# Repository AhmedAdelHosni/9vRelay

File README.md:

# 9vRelay
Relay board operated by 9v. Still in desgning phase.

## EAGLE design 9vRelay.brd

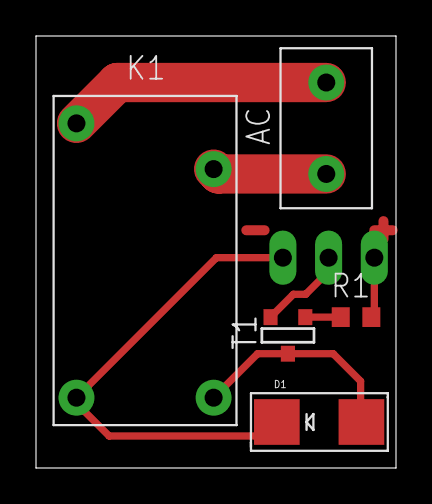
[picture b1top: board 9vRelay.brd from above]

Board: 2 copper layers, 20.0 x 24.0 mm, 6 parts (1 on the bottom side), 7 nets.

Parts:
AC: TBLOCK1X2
D1: SMADIODE
K1: OJE-SS-109LMH
R1: R0603
T1: 2N3904; SOT-23
X1: 22-23-2031

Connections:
unnamed: D1.A, K1.2, T1.1
unnamed: D1.C, K1.1, X1.3
unnamed: R1.1, X1.1
unnamed: AC.2, K1.4
unnamed: T1.2, X1.2
unnamed: R1.2, T1.3
unnamed: AC.1, K1.3

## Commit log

2016-04-08 :octocat: Added .gitattributes & .gitignore files
2016-04-08 initial commit
    initial commit.
    This repository is for designing a relay board powered by 9v.
2016-04-11 Added CERN Open Hardware Licence v1.2 license
    Added CERN Open Hardware Licence v1.2 license
2016-04-13 initial commit
    Schematic and board design completed
2017-09-28 Re orientation and fixes
    Re orientation and fixed the missing input voltage for powering the relay coil
